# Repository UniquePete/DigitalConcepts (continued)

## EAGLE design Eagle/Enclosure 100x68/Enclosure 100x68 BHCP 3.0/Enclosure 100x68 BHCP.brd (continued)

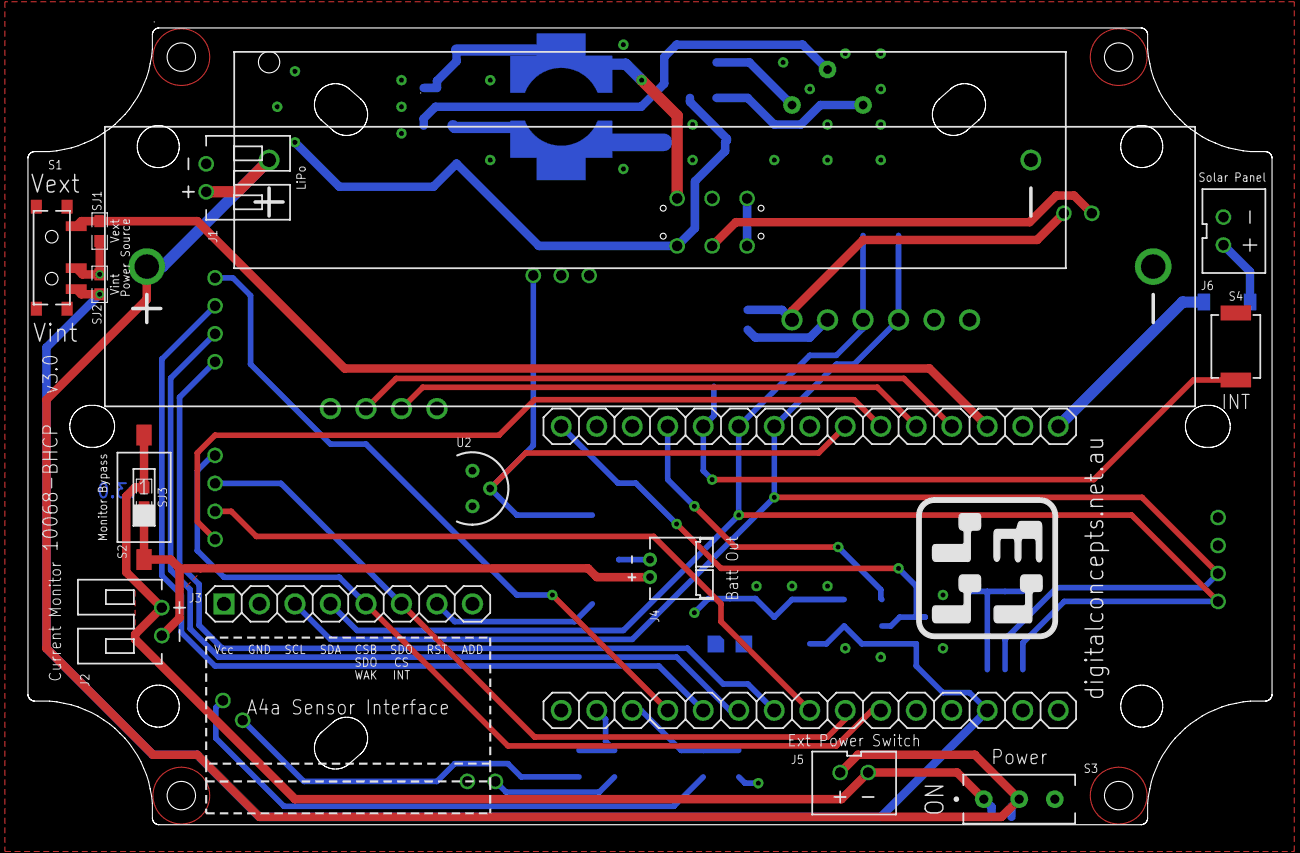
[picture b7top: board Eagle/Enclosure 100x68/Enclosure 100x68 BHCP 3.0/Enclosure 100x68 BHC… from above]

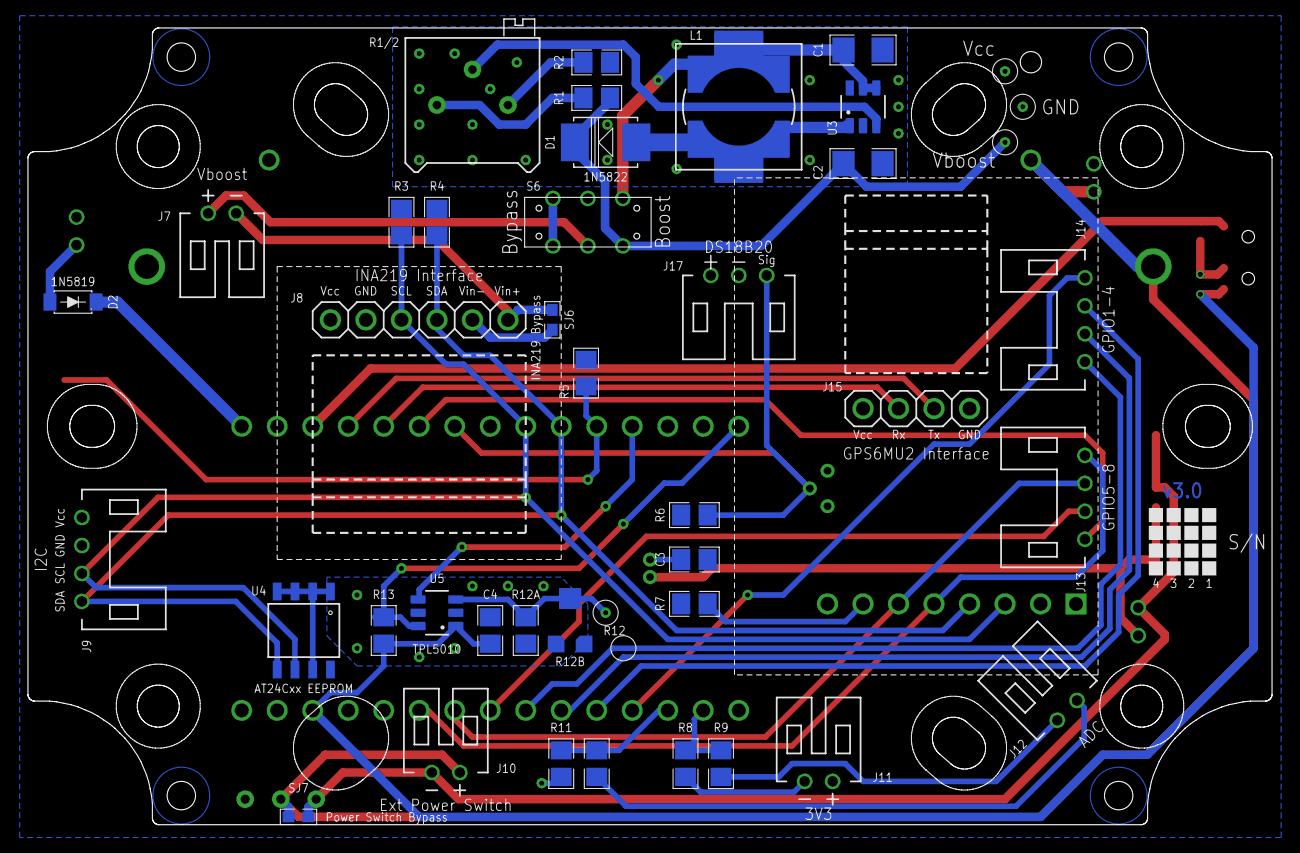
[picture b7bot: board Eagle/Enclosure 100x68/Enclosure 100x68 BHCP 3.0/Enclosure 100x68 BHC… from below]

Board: 2 copper layers, 89.0 x 57.0 mm, 54 parts (38 on the bottom side), 40 nets.
